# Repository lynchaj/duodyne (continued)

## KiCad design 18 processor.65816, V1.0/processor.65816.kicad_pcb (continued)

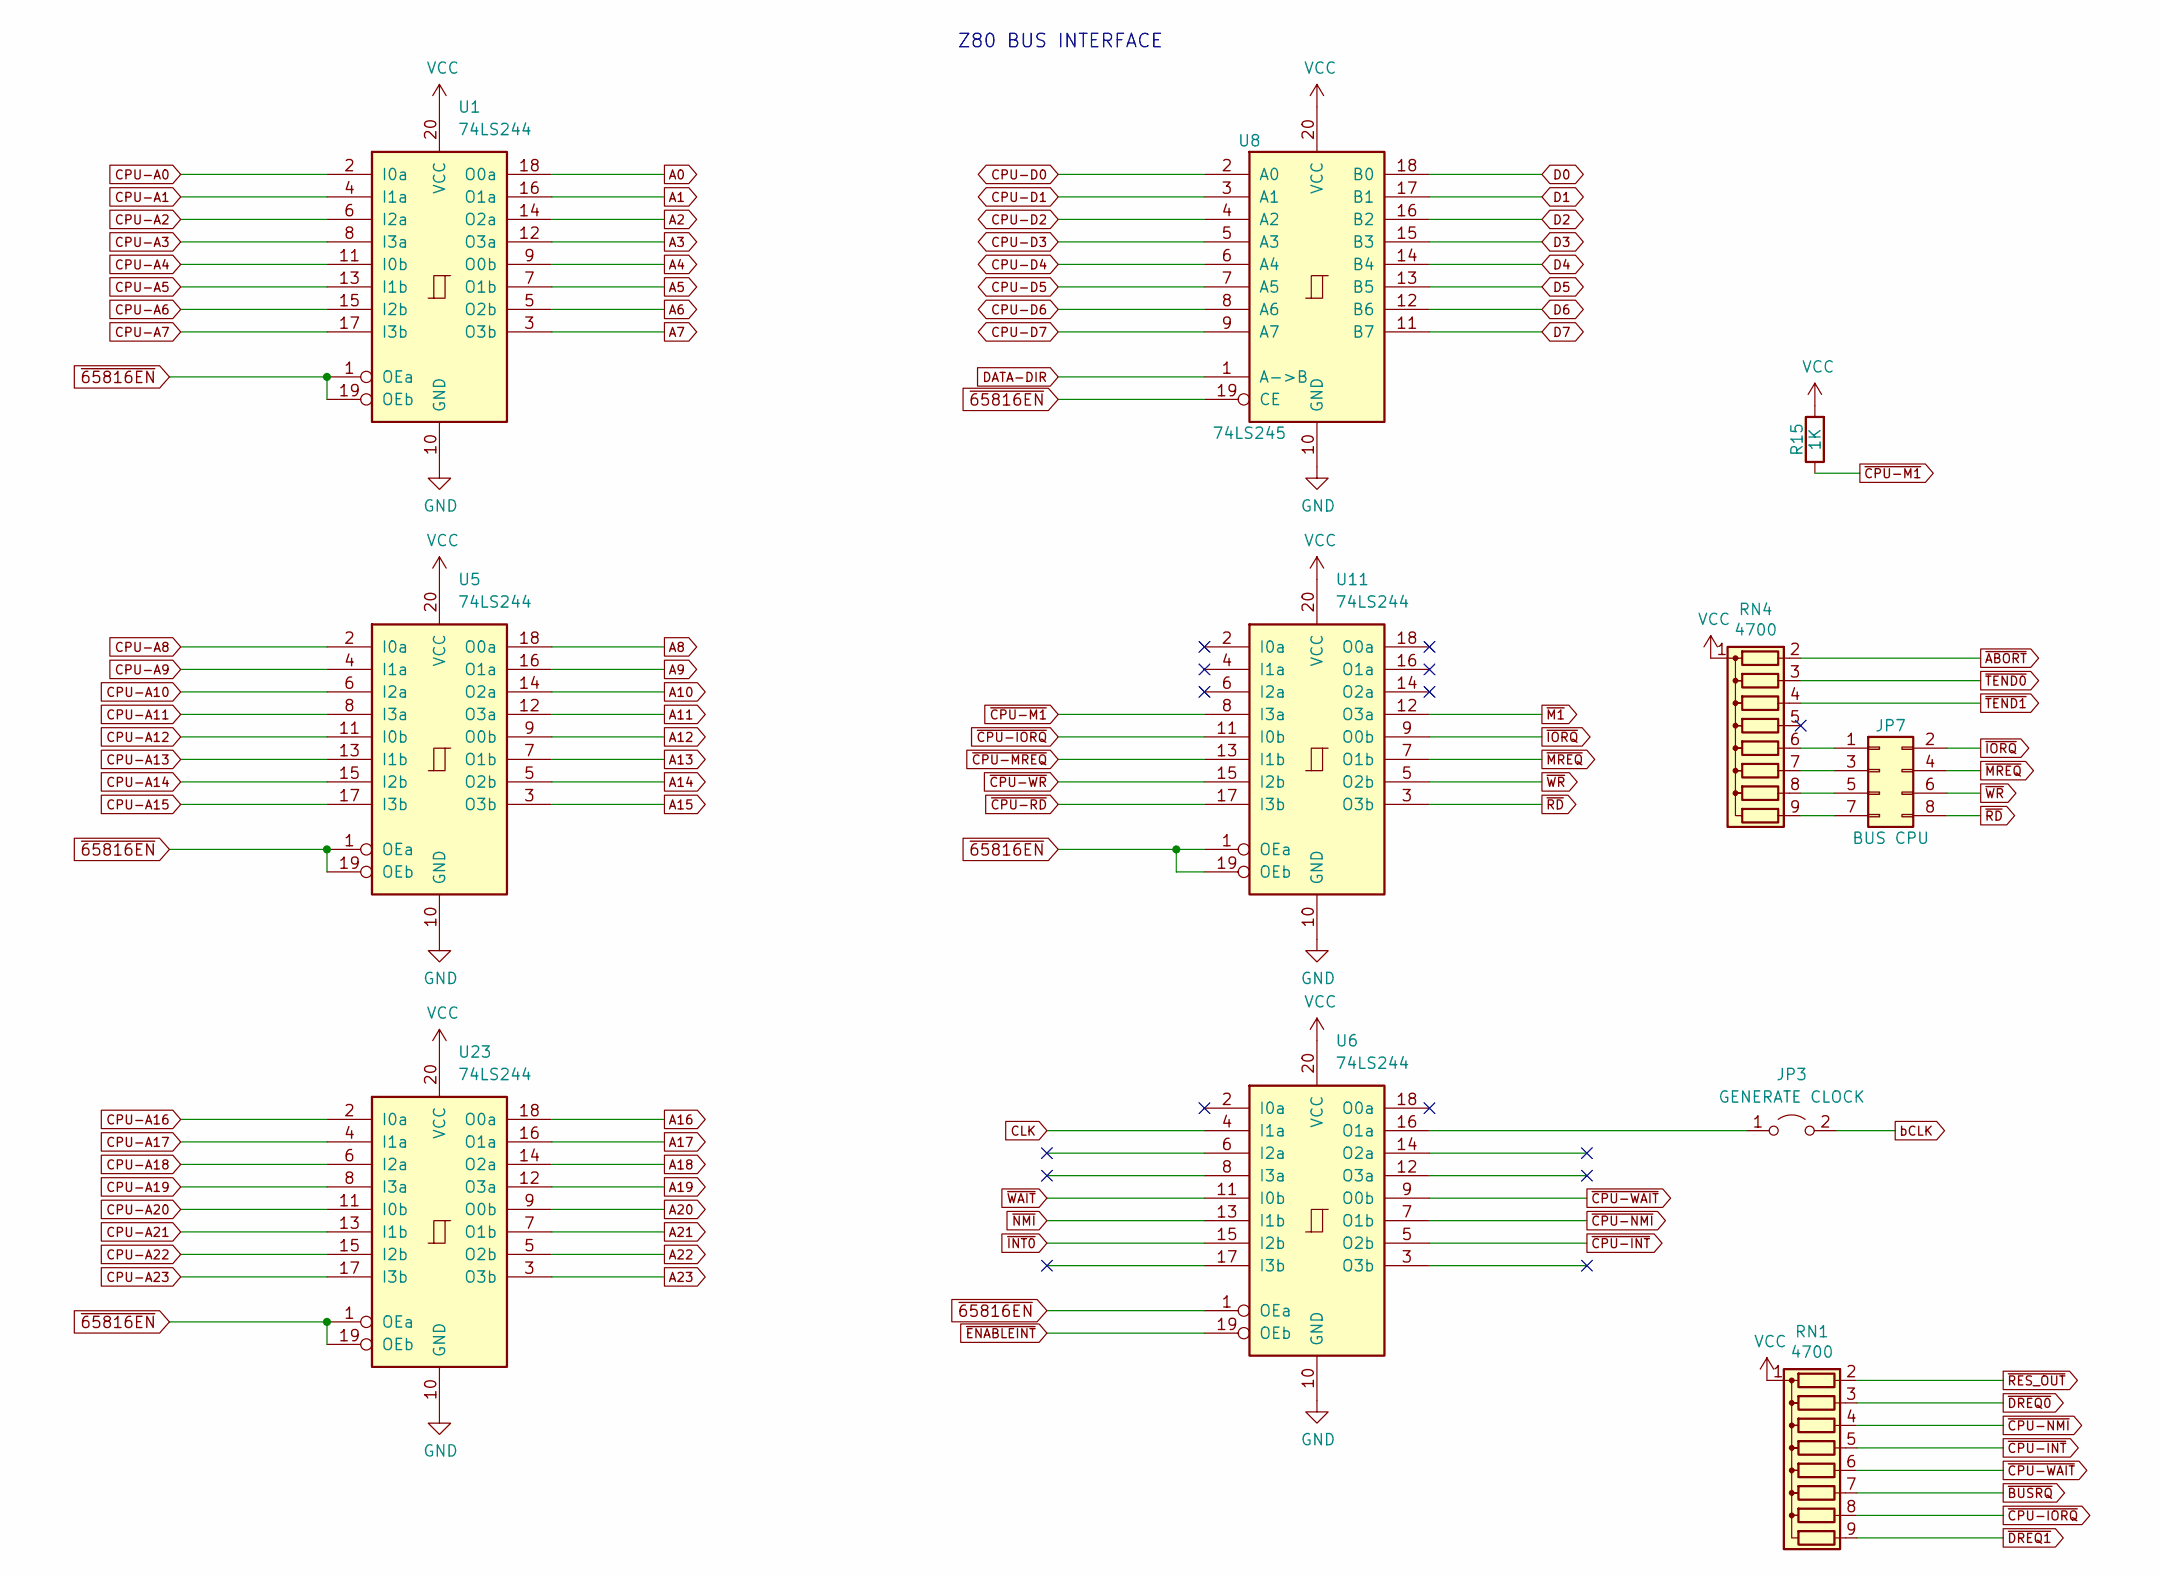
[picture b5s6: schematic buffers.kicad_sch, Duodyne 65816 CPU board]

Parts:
JP3: GENERATE CLOCK; PinHeader_1x02_P2.54mm_Vertical
JP7: BUS CPU; PinHeader_2x04_P2.54mm_Vertical
R15: 1K; R_Axial_DIN0207_L6.3mm_D2.5mm_P7.62mm_Horizontal
RN1, RN4: 4700; R_Array_SIP9
U1, U5, U6, U11, U23: 74LS244; DIP-20_W7.62mm_Socket_LongPads
U8: 74LS245; DIP-20_W7.62mm_Socket_LongPads

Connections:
A0: U1.18 (O0a); also elsewhere on the board
A1: U1.16 (O1a); also elsewhere on the board
A2: U1.14 (O2a); also elsewhere on the board
A3: U1.12 (O3a); also elsewhere on the board
A4: U1.9 (O0b); also elsewhere on the board
A5: U1.7 (O1b); also elsewhere on the board
A6: U1.5 (O2b); also elsewhere on the board
A7: U1.3 (O3b); also elsewhere on the board
A8: U5.18 (O0a); also elsewhere on the board
A9: U5.16 (O1a); also elsewhere on the board
A10: U5.14 (O2a); also elsewhere on the board
A11: U5.12 (O3a); also elsewhere on the board
A12: U5.9 (O0b); also elsewhere on the board
A13: U5.7 (O1b); also elsewhere on the board
A14: U5.5 (O2b); also elsewhere on the board
A15: U5.3 (O3b); also elsewhere on the board
A16: U23.18 (O0a); also elsewhere on the board
A17: U23.16 (O1a); also elsewhere on the board
A18: U23.14 (O2a); also elsewhere on the board
A19: U23.12 (O3a); also elsewhere on the board
A20: U23.9 (O0b); also elsewhere on the board
A21: U23.7 (O1b); also elsewhere on the board
A22: U23.5 (O2b); also elsewhere on the board
A23: U23.3 (O3b); also elsewhere on the board
CLK: U6.4 (I1a); also elsewhere on the board
CPU-A0: U1.2 (I0a); also elsewhere on the board
CPU-A1: U1.4 (I1a); also elsewhere on the board
CPU-A2: U1.6 (I2a); also elsewhere on the board
CPU-A3: U1.8 (I3a); also elsewhere on the board
CPU-A4: U1.11 (I0b); also elsewhere on the board
CPU-A5: U1.13 (I1b); also elsewhere on the board
CPU-A6: U1.15 (I2b); also elsewhere on the board
CPU-A7: U1.17 (I3b); also elsewhere on the board
CPU-A8: U5.2 (I0a); also elsewhere on the board
CPU-A9: U5.4 (I1a); also elsewhere on the board
CPU-A10: U5.6 (I2a); also elsewhere on the board
CPU-A11: U5.8 (I3a); also elsewhere on the board
CPU-A12: U5.11 (I0b); also elsewhere on the board
CPU-A13: U5.13 (I1b); also elsewhere on the board
CPU-A14: U5.15 (I2b); also elsewhere on the board
CPU-A15: U5.17 (I3b); also elsewhere on the board
CPU-A16: U23.2 (I0a); also elsewhere on the board
CPU-A17: U23.4 (I1a); also elsewhere on the board
CPU-A18: U23.6 (I2a); also elsewhere on the board
CPU-A19: U23.8 (I3a); also elsewhere on the board
CPU-A20: U23.11 (I0b); also elsewhere on the board
CPU-A21: U23.13 (I1b); also elsewhere on the board
CPU-A22: U23.15 (I2b); also elsewhere on the board
CPU-A23: U23.17 (I3b); also elsewhere on the board
CPU-D0: U8.2 (A0); also elsewhere on the board
CPU-D1: U8.3 (A1); also elsewhere on the board
CPU-D2: U8.4 (A2); also elsewhere on the board
CPU-D3: U8.5 (A3); also elsewhere on the board
CPU-D4: U8.6 (A4); also elsewhere on the board
CPU-D5: U8.7 (A5); also elsewhere on the board
CPU-D6: U8.8 (A6); also elsewhere on the board
CPU-D7: U8.9 (A7); also elsewhere on the board
D0: U8.18 (B0); also elsewhere on the board
D1: U8.17 (B1); also elsewhere on the board
D2: U8.16 (B2); also elsewhere on the board
D3: U8.15 (B3); also elsewhere on the board
D4: U8.14 (B4); also elsewhere on the board
D5: U8.13 (B5); also elsewhere on the board
D6: U8.12 (B6); also elsewhere on the board
D7: U8.11 (B7); also elsewhere on the board
DATA-DIR: U8.1 (A->B); also elsewhere on the board
GND: U1.10 (GND), U5.10 (GND), U6.10 (GND), U8.10 (GND), U11.10 (GND), U23.10 (GND); also elsewhere on the board
unnamed: JP3.1 (A), U6.16 (O1a)
unnamed: JP7.1, RN4.6 (R5)
unnamed: JP7.3, RN4.7 (R6)
unnamed: JP7.5, RN4.8 (R7)
unnamed: JP7.7, RN4.9 (R8)
VCC: R15.2, RN1.1 (common), RN4.1 (common), U1.20 (VCC), U5.20 (VCC), U6.20 (VCC), U8.20 (VCC), U11.20 (VCC), U23.20 (VCC); also elsewhere on the board
bCLK: JP3.2 (B); also elsewhere on the board
~65816EN: U1.1 (OEa), U1.19 (OEb), U5.1 (OEa), U5.19 (OEb), U6.1 (OEa), U8.19 (CE), U11.1 (OEa), U11.19 (OEb), U23.1 (OEa), U23.19 (OEb); also elsewhere on the board
~ABORT: RN4.2 (R1); also elsewhere on the board
~BUSRQ: RN1.7 (R6); also elsewhere on the board
~CPU-INT: RN1.5 (R4), U6.5 (O2b); also elsewhere on the board
~CPU-IORQ: RN1.8 (R7), U11.11 (I0b); also elsewhere on the board
~CPU-M1: R15.1, U11.8 (I3a)
~CPU-MREQ: U11.13 (I1b); also elsewhere on the board
~CPU-NMI: RN1.4 (R3), U6.7 (O1b); also elsewhere on the board
~CPU-RD: U11.17 (I3b); also elsewhere on the board
~CPU-WAIT: RN1.6 (R5), U6.9 (O0b); also elsewhere on the board
~CPU-WR: U11.15 (I2b); also elsewhere on the board
~DREQ0: RN1.3 (R2); also elsewhere on the board
~DREQ1: RN1.9 (R8); also elsewhere on the board
~ENABLEINT: U6.19 (OEb); also elsewhere on the board
~INT0: U6.15 (I2b); also elsewhere on the board
~IORQ: JP7.2, U11.9 (O0b); also elsewhere on the board
~M1: U11.12 (O3a); also elsewhere on the board
~MREQ: JP7.4, U11.7 (O1b); also elsewhere on the board
~NMI: U6.13 (I1b); also elsewhere on the board
~RD: JP7.8, U11.3 (O3b); also elsewhere on the board
~RES_OUT: RN1.2 (R1); also elsewhere on the board
~TEND0: RN4.3 (R2); also elsewhere on the board
~TEND1: RN4.4 (R3); also elsewhere on the board
~WAIT: U6.11 (I0b); also elsewhere on the board
~WR: JP7.6, U11.5 (O2b); also elsewhere on the board

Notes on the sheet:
Z80 BUS INTERFACE

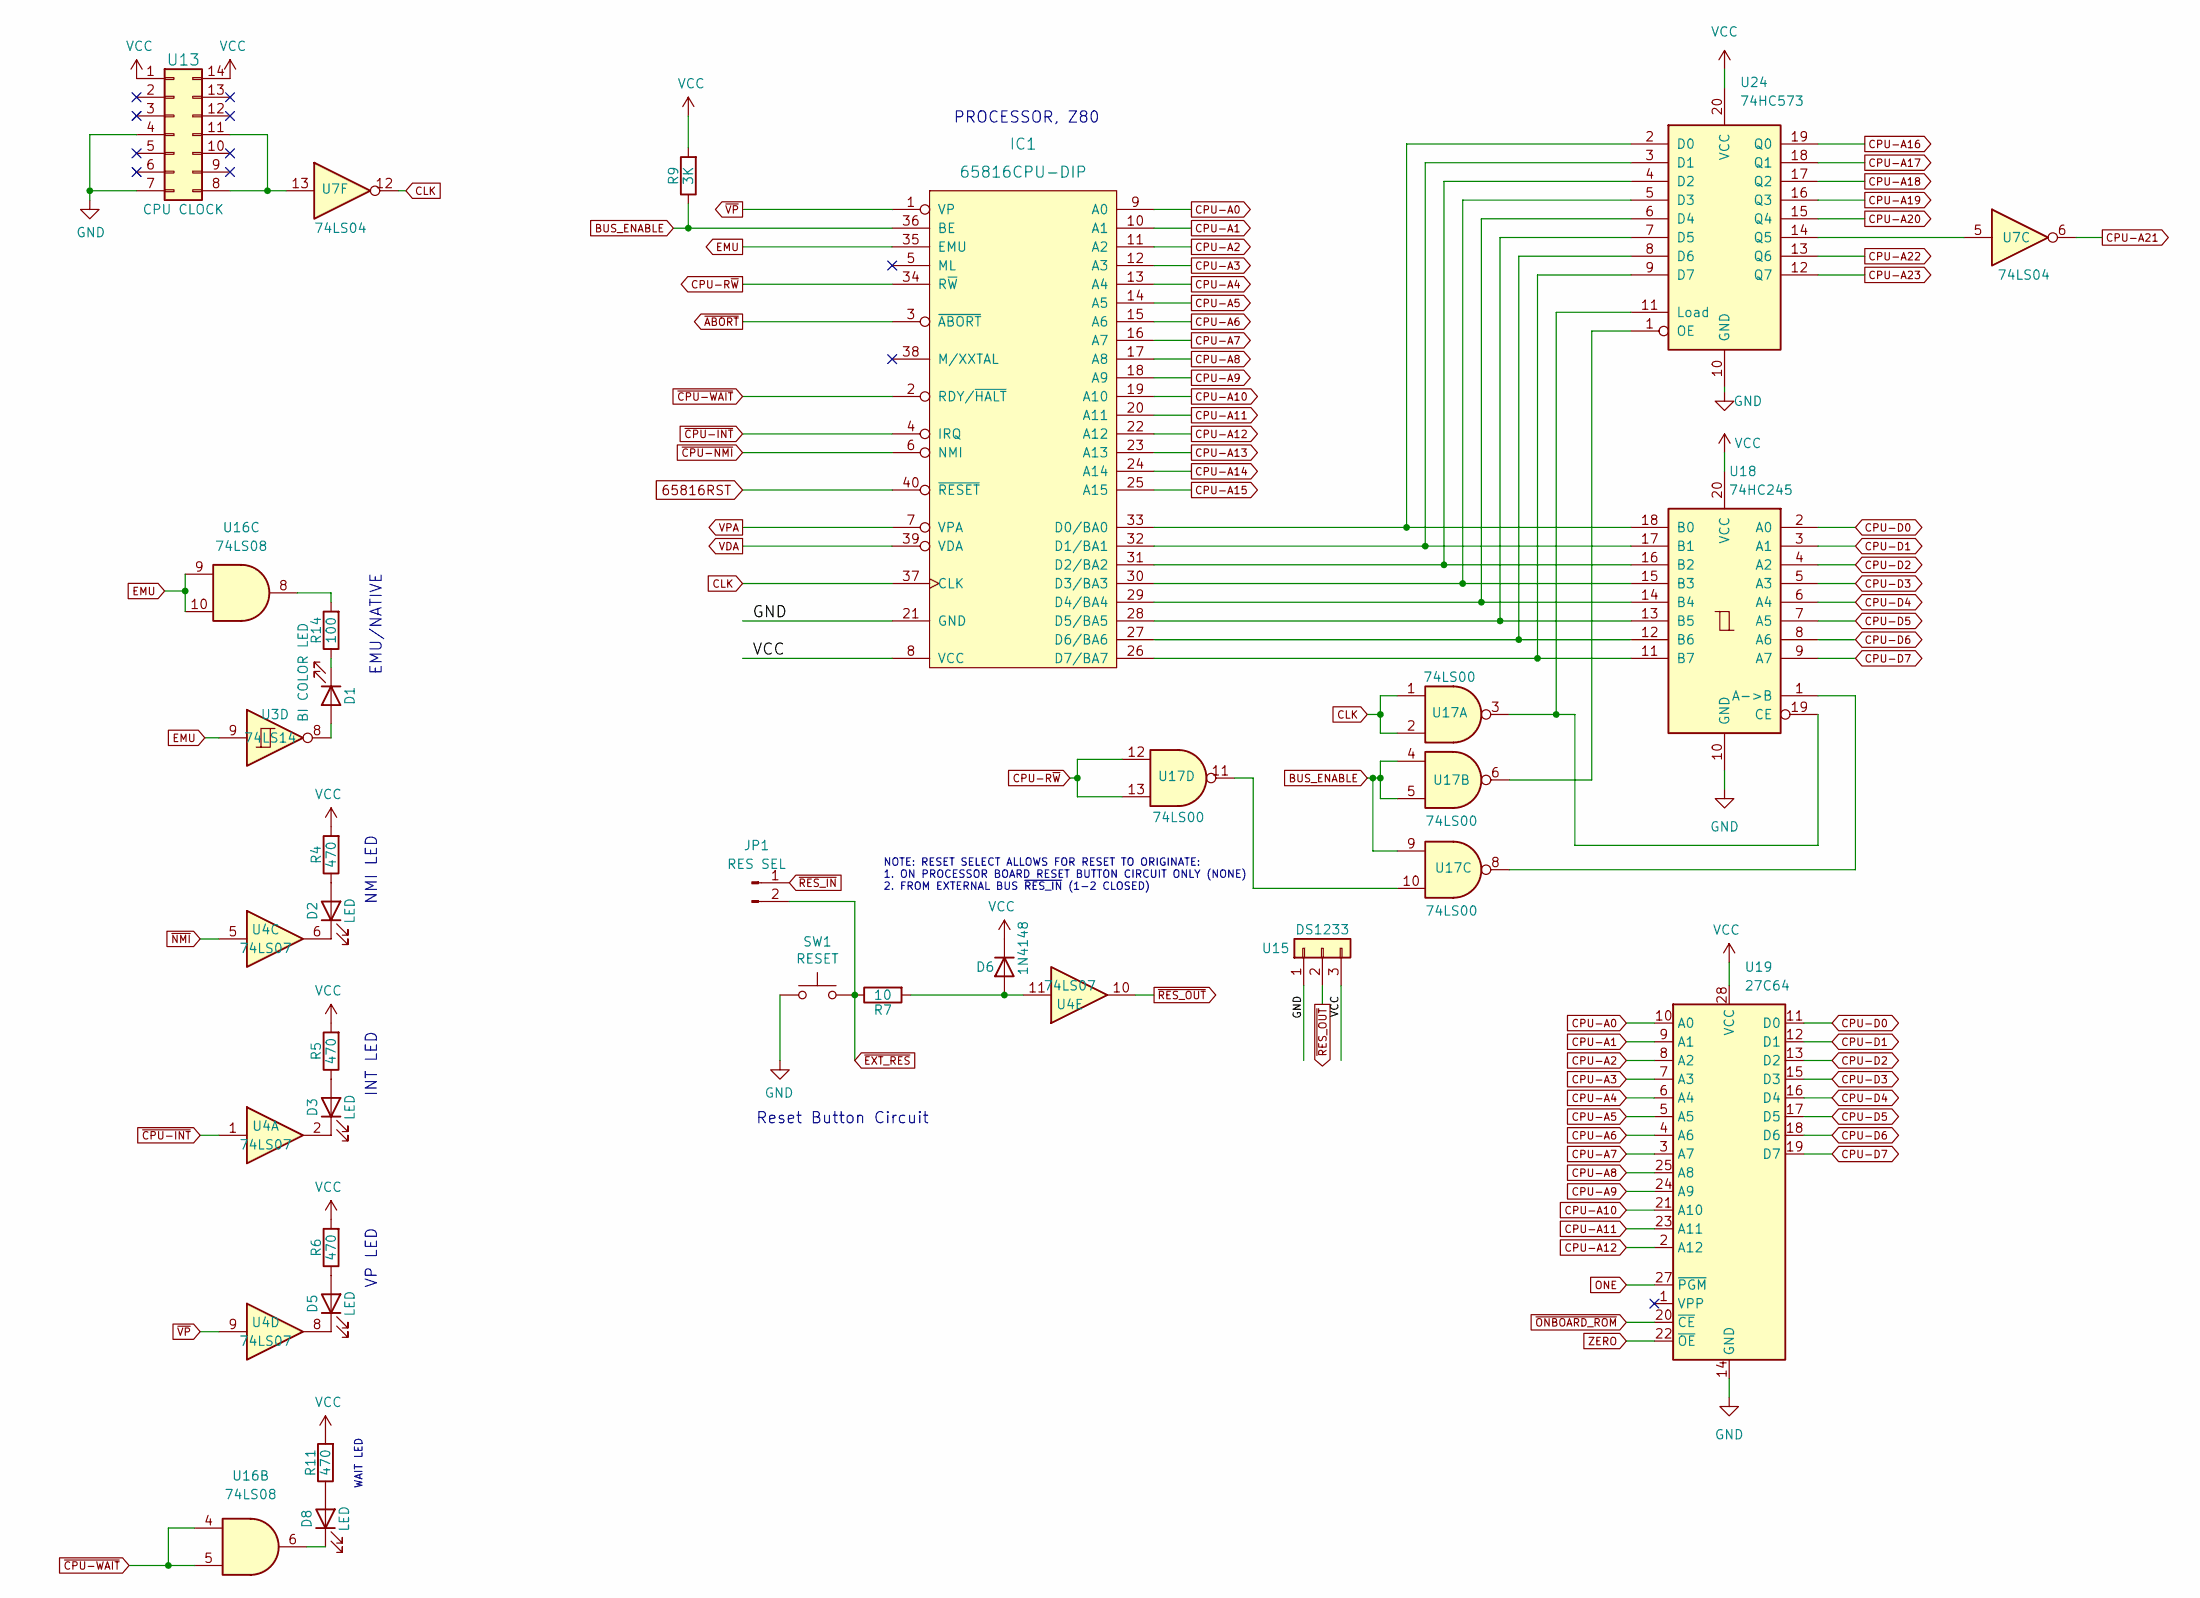
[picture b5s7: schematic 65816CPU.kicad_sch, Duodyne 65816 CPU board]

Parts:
D1: BI COLOR LED; LED_D3.0mm_Horizontal_O3.81mm_Z2.0mm
D2, D3, D5, D8: LED; LED_D3.0mm_Horizontal_O3.81mm_Z2.0mm
D6: 1N4148; D_DO-35_SOD27_P7.62mm_Horizontal
IC1: 65816CPU-DIP; DIP-40_W15.24mm_Socket_LongPads
JP1: RES SEL; PinHeader_1x02_P2.54mm_Vertical
R4, R5, R6, R11: 470; R_Axial_DIN0207_L6.3mm_D2.5mm_P7.62mm_Horizontal
R7: 10; R_Axial_DIN0207_L6.3mm_D2.5mm_P7.62mm_Horizontal
R9: 3K; R_Axial_DIN0207_L6.3mm_D2.5mm_P7.62mm_Horizontal
R14: 100; R_Axial_DIN0207_L6.3mm_D2.5mm_P7.62mm_Horizontal
SW1: RESET; SW_Tactile_SPST_Angled_PTS645Vx58-2LFS
U3: 74LS14; DIP-14_W7.62mm_Socket_LongPads
U4: 74LS07; DIP-14_W7.62mm_Socket_LongPads
U7: 74LS04; DIP-14_W7.62mm_Socket_LongPads
U13: CPU CLOCK; DIP-14_W7.62mm_Socket_LongPads
U15: DS1233; TO-92L_HandSolder
U16: 74LS08; DIP-14_W7.62mm_Socket_LongPads
U17: 74LS00; DIP-14_W7.62mm_Socket_LongPads
U18: 74HC245; DIP-20_W7.62mm_Socket_LongPads
U19: 27C64; DIP-28_W15.24mm_Socket_LongPads
U24: 74HC573; DIP-20_W7.62mm_Socket_LongPads

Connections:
65816RST: IC1.40 (~RESET); also elsewhere on the board
BUS_ENABLE: IC1.36 (BE), R9.1, U17.4, U17.5, U17.9
CLK: IC1.37 (CLK), U7.12, U17.1, U17.2; also elsewhere on the board
CPU-A0: IC1.9 (A0), U19.10 (A0); also elsewhere on the board
CPU-A1: IC1.10 (A1), U19.9 (A1); also elsewhere on the board
CPU-A2: IC1.11 (A2), U19.8 (A2); also elsewhere on the board
CPU-A3: IC1.12 (A3), U19.7 (A3); also elsewhere on the board
CPU-A4: IC1.13 (A4), U19.6 (A4); also elsewhere on the board
CPU-A5: IC1.14 (A5), U19.5 (A5); also elsewhere on the board
CPU-A6: IC1.15 (A6), U19.4 (A6); also elsewhere on the board
CPU-A7: IC1.16 (A7), U19.3 (A7); also elsewhere on the board
CPU-A8: IC1.17 (A8), U19.25 (A8); also elsewhere on the board
CPU-A9: IC1.18 (A9), U19.24 (A9); also elsewhere on the board
CPU-A10: IC1.19 (A10), U19.21 (A10); also elsewhere on the board
CPU-A11: IC1.20 (A11), U19.23 (A11); also elsewhere on the board
CPU-A12: IC1.22 (A12), U19.2 (A12); also elsewhere on the board
CPU-A13: IC1.23 (A13); also elsewhere on the board
CPU-A14: IC1.24 (A14); also elsewhere on the board
CPU-A15: IC1.25 (A15); also elsewhere on the board
CPU-A16: U24.19 (Q0); also elsewhere on the board
CPU-A17: U24.18 (Q1); also elsewhere on the board
CPU-A18: U24.17 (Q2); also elsewhere on the board
CPU-A19: U24.16 (Q3); also elsewhere on the board
CPU-A20: U24.15 (Q4); also elsewhere on the board
CPU-A21: U7.6; also elsewhere on the board
CPU-A22: U24.13 (Q6); also elsewhere on the board
CPU-A23: U24.12 (Q7); also elsewhere on the board
CPU-D0: U18.2 (A0), U19.11 (D0); also elsewhere on the board
CPU-D1: U18.3 (A1), U19.12 (D1); also elsewhere on the board
CPU-D2: U18.4 (A2), U19.13 (D2); also elsewhere on the board
CPU-D3: U18.5 (A3), U19.15 (D3); also elsewhere on the board
CPU-D4: U18.6 (A4), U19.16 (D4); also elsewhere on the board
CPU-D5: U18.7 (A5), U19.17 (D5); also elsewhere on the board
CPU-D6: U18.8 (A6), U19.18 (D6); also elsewhere on the board
CPU-D7: U18.9 (A7), U19.19 (D7); also elsewhere on the board
CPU-R~W: IC1.34 (R~W), U17.12, U17.13; also elsewhere on the board
EMU: IC1.35 (EMU), U3.9, U16.9, U16.10
GND: IC1.21 (GND), SW1.2, U13.4, U13.7, U15.1, U18.10 (GND), U19.14 (GND), U24.10 (GND); also elsewhere on the board
unnamed: D1.1 (K), R14.1
unnamed: D1.2 (A), U3.8
unnamed: D2.1 (K), U4.6
unnamed: D2.2 (A), R4.1
unnamed: D3.1 (K), U4.2
unnamed: D3.2 (A), R5.1
unnamed: D5.1 (K), U4.8
unnamed: D5.2 (A), R6.1
unnamed: D6.2 (A), R7.2, U4.11
unnamed: D8.1 (K), U16.6
unnamed: D8.2 (A), R11.1
unnamed: IC1.26 (D7/BA7), U18.11 (B7), U24.9 (D7)
unnamed: IC1.27 (D6/BA6), U18.12 (B6), U24.8 (D6)
unnamed: IC1.28 (D5/BA5), U18.13 (B5), U24.7 (D5)
unnamed: IC1.29 (D4/BA4), U18.14 (B4), U24.6 (D4)
unnamed: IC1.30 (D3/BA3), U18.15 (B3), U24.5 (D3)
unnamed: IC1.31 (D2/BA2), U18.16 (B2), U24.4 (D2)
unnamed: IC1.32 (D1/BA1), U18.17 (B1), U24.3 (D1)
unnamed: IC1.33 (D0/BA0), U18.18 (B0), U24.2 (D0)
unnamed: R14.2, U16.8
unnamed: U7.13, U13.8, U13.11
unnamed: U17.3, U18.19 (CE), U24.11 (Load)
unnamed: U17.6, U24.1 (OE)
unnamed: U17.8, U18.1 (A->B)
unnamed: U17.10, U17.11
unnamed: U7.5, U24.14 (Q5)
ONE: U19.27 (~PGM); also elsewhere on the board
VCC: D6.1 (K), IC1.8 (VCC), R4.2, R5.2, R6.2, R9.2, R11.2, U13.1, U13.14, U15.3, U18.20 (VCC), U19.28 (VCC), U24.20 (VCC); also elsewhere on the board
VDA: IC1.39 (VDA); also elsewhere on the board
VPA: IC1.7 (VPA); also elsewhere on the board
ZERO: U19.22 (~OE); also elsewhere on the board
~ABORT: IC1.3 (~ABORT); also elsewhere on the board
~CPU-INT: IC1.4 (IRQ), U4.1; also elsewhere on the board
~CPU-NMI: IC1.6 (NMI); also elsewhere on the board
~CPU-WAIT: IC1.2 (RDY/~HALT), U16.4, U16.5; also elsewhere on the board
~EXT_RES: JP1.2, R7.1, SW1.1; also elsewhere on the board
~NMI: U4.5; also elsewhere on the board
~ONBOARD_ROM: U19.20 (~CE); also elsewhere on the board
~RES_IN: JP1.1; also elsewhere on the board
~RES_OUT: U4.10, U15.2; also elsewhere on the board
~VP: IC1.1 (VP), U4.9

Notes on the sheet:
PROCESSOR, Z80
VP LED
Reset Button Circuit
WAIT LED
NMI LED
INT LED
NOTE: RESET SELECT ALLOWS FOR RESET TO ORIGINATE: 1. ON PROCESSOR BOARD RESET BUTTON CIRCUIT ONLY (NONE) 2. FROM EXTERNAL BUS ~{RES_IN} (1-2 CLOSED)
EMU/NATIVE

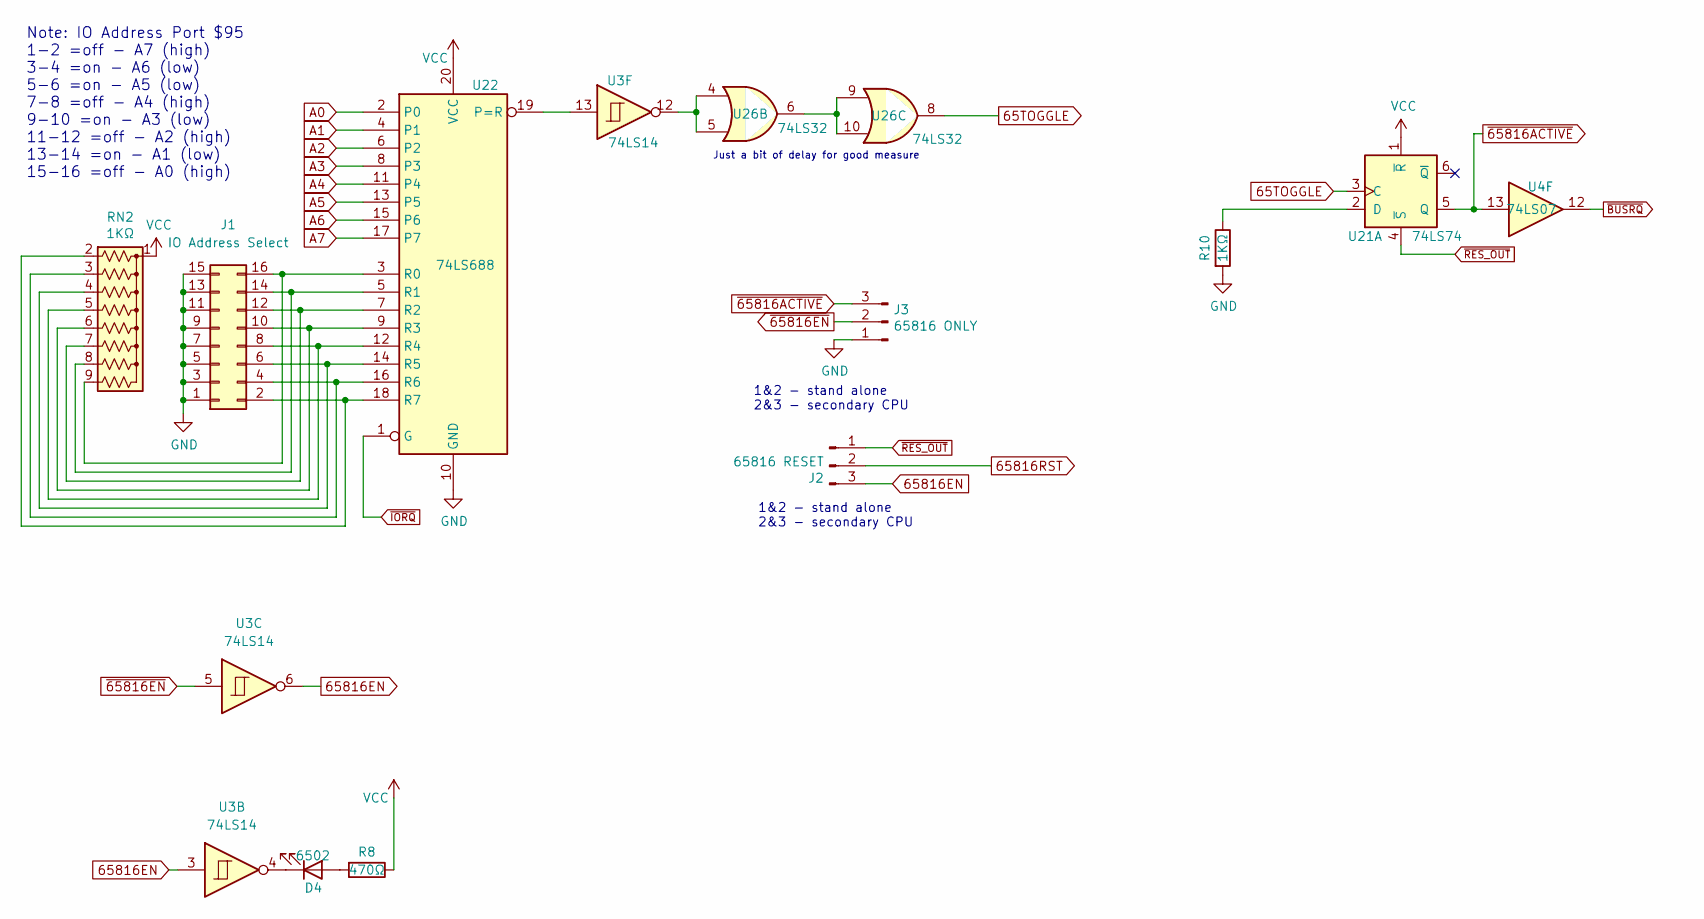
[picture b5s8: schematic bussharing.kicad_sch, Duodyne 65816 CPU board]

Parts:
D4: 6502; LED_D3.0mm_Horizontal_O3.81mm_Z2.0mm
J1: IO Address Select; PinHeader_2x08_P2.54mm_Vertical
J2: 65816 RESET; PinHeader_1x03_P2.54mm_Horizontal
J3: 65816 ONLY; PinHeader_1x03_P2.54mm_Horizontal
R8: 470Ω; R_Axial_DIN0207_L6.3mm_D2.5mm_P7.62mm_Horizontal
R10: 1KΩ; R_Axial_DIN0207_L6.3mm_D2.5mm_P7.62mm_Horizontal
RN2: 1KΩ; R_Array_SIP9
U3: 74LS14; DIP-14_W7.62mm_Socket_LongPads
U4: 74LS07; DIP-14_W7.62mm_Socket_LongPads
U21: 74LS74; DIP-14_W7.62mm_Socket_LongPads
U22: 74LS688; DIP-20_W7.62mm_Socket_LongPads
U26: 74LS32; DIP-14_W7.62mm_Socket_LongPads

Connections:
65TOGGLE: U21.3 (C), U26.8
65816EN: J2.3, U3.3, U3.6
65816RST: J2.2; also elsewhere on the board
A0: U22.2 (P0); also elsewhere on the board
A1: U22.4 (P1); also elsewhere on the board
A2: U22.6 (P2); also elsewhere on the board
A3: U22.8 (P3); also elsewhere on the board
A4: U22.11 (P4); also elsewhere on the board
A5: U22.13 (P5); also elsewhere on the board
A6: U22.15 (P6); also elsewhere on the board
A7: U22.17 (P7); also elsewhere on the board
GND: J1.1, J1.3, J1.5, J1.7, J1.9, J1.11, J1.13, J1.15, J3.1, R10.2, U22.10 (GND); also elsewhere on the board
unnamed: D4.1 (K), U3.4
unnamed: D4.2 (A), R8.2
unnamed: J1.2, RN2.2 (R1), U22.18 (R7)
unnamed: J1.4, RN2.3 (R2), U22.16 (R6)
unnamed: J1.6, RN2.4 (R3), U22.14 (R5)
unnamed: J1.8, RN2.5 (R4), U22.12 (R4)
unnamed: J1.10, RN2.6 (R5), U22.9 (R3)
unnamed: J1.12, RN2.7 (R6), U22.7 (R2)
unnamed: J1.14, RN2.8 (R7), U22.5 (R1)
unnamed: J1.16, RN2.9 (R8), U22.3 (R0)
unnamed: R10.1, U21.2 (D)
unnamed: U3.13, U22.19 (P=R)
unnamed: U3.12, U26.4, U26.5
unnamed: U26.6, U26.9, U26.10
VCC: R8.1, RN2.1 (common), U21.1 (~R), U22.20 (VCC); also elsewhere on the board
~65816ACTIVE: J3.3, U4.13, U21.5 (Q)
~65816EN: J3.2, U3.5; also elsewhere on the board
~BUSRQ: U4.12; also elsewhere on the board
~IORQ: U22.1 (G); also elsewhere on the board
~RES_OUT: J2.1, U21.4 (~S); also elsewhere on the board

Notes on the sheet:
1&2 - stand alone 2&3 - secondary CPU
Note: IO Address Port $95 1-2 =off - A7 (high) 3-4 =on - A6 (low) 5-6 =on - A5 (low) 7-8 =off - A4 (high) 9-10 =on - A3 (low) 11-12 =off - A2 (high) 13-14 =on - A1 (low) 15-16 =off - A0 (high)
Just a bit of delay for good measure

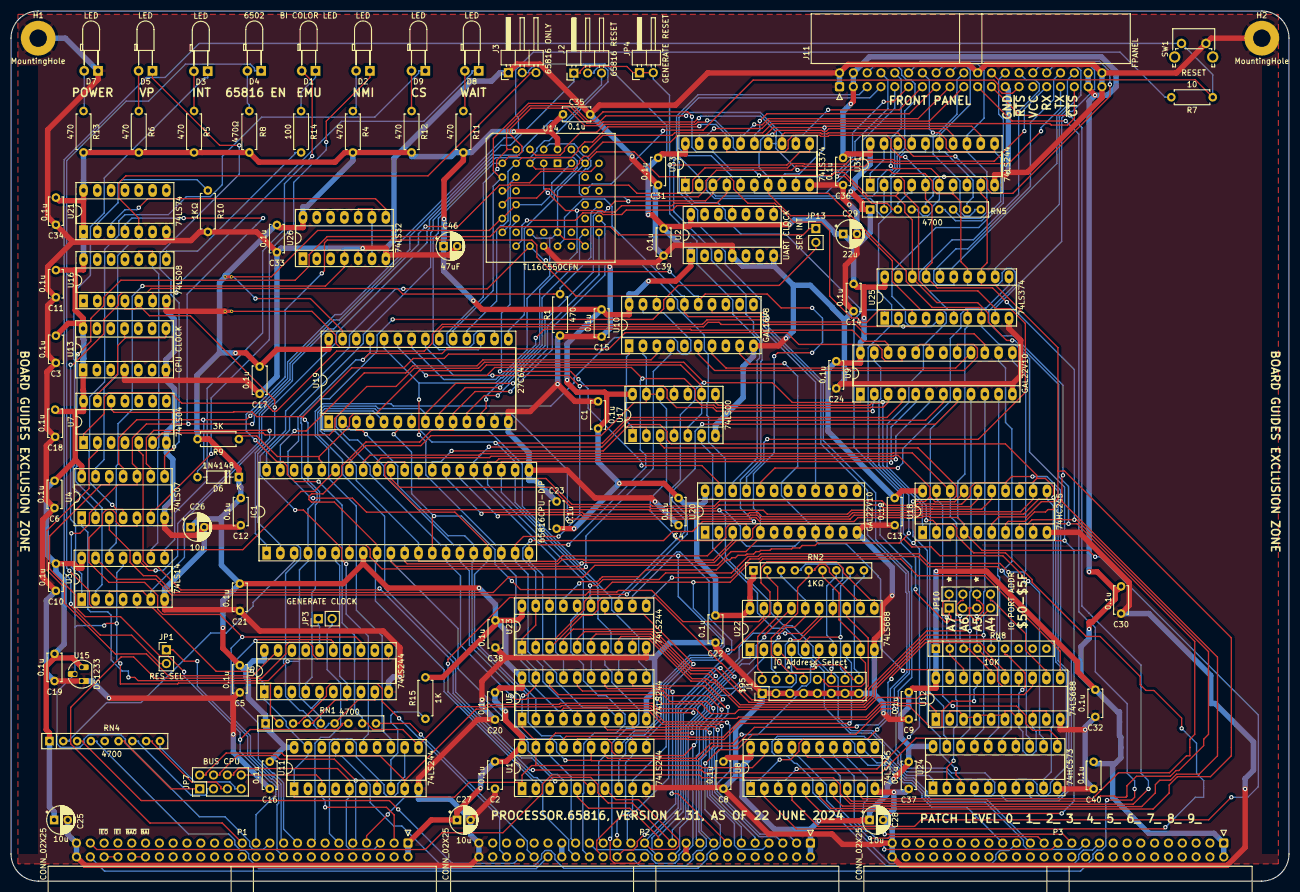
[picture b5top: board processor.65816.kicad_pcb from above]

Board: 2 copper layers, 235.0 x 160.0 mm, 114 parts (0 on the bottom side), 208 nets.

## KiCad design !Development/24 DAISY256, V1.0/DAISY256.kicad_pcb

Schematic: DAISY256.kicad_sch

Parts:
C1, C2, C3, C5, C13, C20, C21, C22, C23, C24, C25, C26, C27, C28, C29, C32, C33, C34, C35: 100nF; C_Disc_D5.0mm_W2.5mm_P5.00mm
C4, C8: 220uF; CP_Radial_D6.3mm_P2.50mm
C6, C7, C14, C15: 22pF; C_Disc_D5.0mm_W2.5mm_P5.00mm
C9, C12, C17, C18, C19: 47nF; C_Disc_D5.0mm_W2.5mm_P5.00mm
C10, C11, C30: 10uF; CP_Radial_D5.0mm_P2.00mm
C16: 22nF; C_Disc_D5.0mm_W2.5mm_P5.00mm
C31: 2.2uF; CP_Radial_Tantal_D5.0mm_P2.50mm
D1: BUSY; LED_D3.0mm
H1, H2, H3, H4: MountingHole_Pad; MountingHole_3.2mm_M3_Pad
J1: DC_JACK; BarrelJack_Horizontal
J2: DE9; DSUB-9_Female_Horizontal_P2.77x2.84mm_EdgePinOffset7.70mm_H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
J3: Audio Out; Jack_3.5mm_CUI_SJ1-3544_Horizontal
J4: TxE; PinHeader_1x02_P2.54mm_Vertical
J5: SPKR; Molex_KK-254_AE-6410-02A_1x02_P2.54mm_Vertical
J6: 32/16; PinHeader_1x03_P2.54mm_Vertical
J7: MODE; PinHeader_1x02_P2.54mm_Vertical
J8: DBM; PinHeader_1x02_P2.54mm_Vertical
J9, J12: DIL14; DIP-14_W7.62mm_Socket_LongPads
J10, J13: DIL16; DIP-16_W7.62mm_Socket_LongPads
J11, J14: DIL20; DIP-20_W7.62mm_Socket_LongPads
J15: SER ROM; PinHeader_2x04_P2.54mm_Vertical
J16: PIC ROM; PinHeader_2x08_P2.54mm_Vertical
NT1: NetTie_2; NetTie-2_THT_Pad0.3mm
P1: 10K; Potentiometer_Bourns_PTV111-1_Single_Horizontal
R1, R4, R6, R7, R14, R15, R21: 10K; R_Axial_DIN0207_L6.3mm_D2.5mm_P7.62mm_Horizontal
R2, R5, R8, R9, R10, R11, R12, R19, R20: 4.7K; R_Axial_DIN0207_L6.3mm_D2.5mm_P7.62mm_Horizontal
R13: 10R; R_Axial_DIN0207_L6.3mm_D2.5mm_P7.62mm_Horizontal
R16, R17: 1K; R_Axial_DIN0207_L6.3mm_D2.5mm_P7.62mm_Horizontal
R18: 20K; R_Axial_DIN0207_L6.3mm_D2.5mm_P7.62mm_Horizontal
SW1: RESET; SW_PUSH_6mm
U1: CTS256A-AL2; DIP-40_W15.24mm_Socket_LongPads
U2: 74LS373; DIP-20_W7.62mm_Socket_LongPads
U3, U12: 74LS138; DIP-16_W7.62mm_Socket_LongPads
U4: SP0256A-AL2; DIP-28_W15.24mm_Socket_LongPads
U5: LM324; DIP-14_W7.62mm_Socket_LongPads
U6: LM386; DIP-8_W7.62mm_Socket_LongPads
U7: MAX232; DIP-16_W7.62mm_Socket_LongPads
U8: 74LS14; DIP-14_W7.62mm_Socket_LongPads
U9: ICL7660; DIP-8_W7.62mm_Socket_LongPads
U10, U13: 2732; DIP-24_W15.24mm_Socket_LongPads
U11: 6116; DIP-24_W15.24mm_Socket_LongPads
U14: 24LC16; DIP-8_W7.62mm_Socket_LongPads
U15: PIC16F685-IP; DIP-20_W7.62mm_Socket_LongPads
U16: GAL16V8; DIP-20_W7.62mm_Socket_LongPads
Y1: 10MHz; Crystal_HC49-4H_Vertical
Y2: 3.12MHz; Crystal_HC49-U_Vertical

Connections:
-5V: C30.2, U5.11 (V-), U9.5 (VOUT)
/A0: U2.2 (O0), U4.18 (A1), U10.8 (A0), U11.8 (A0), U13.8 (A0)
/A1: U2.5 (O1), U4.17 (A2), U10.7 (A1), U11.7 (A1), U13.7 (A1)
/A2: U2.6 (O2), U4.16 (A3), U10.6 (A2), U11.6 (A2), U13.6 (A2)
/A3: U2.9 (O3), U4.15 (A4), U10.5 (A3), U11.5 (A3), U13.5 (A3)
/A4: U2.12 (O4), U4.14 (A5), U10.4 (A4), U11.4 (A4), U13.4 (A4)
/A5: U2.15 (O5), U4.13 (A6), U10.3 (A5), U11.3 (A5), U13.3 (A5)
/A6: U2.16 (O6), U4.11 (A7), U10.2 (A6), U11.2 (A6), U13.2 (A6)
/A7: U2.19 (O7), U4.10 (A8), U10.1 (A7), U11.1 (A7), U13.1 (A7)
/A8: U1.27 (A8), U10.23 (A8), U11.23 (A8), U13.23 (A8)
/A9: U1.26 (A9), U10.22 (A9), U11.22 (A9), U13.22 (A9)
/A10: U1.24 (A10), U10.19 (A10), U11.19 (A10), U13.19 (A10)
/A11: J6.1, U1.23 (A11), U13.21 (A11)
/A12: U1.22 (A12), U3.1 (A0), U12.1 (A0)
/A13: U1.21 (A13), U3.2 (A1), U12.2 (A1)
/A14: U1.20 (A14), U3.3 (A2), U12.3 (A2)
/A15: U1.19 (A15), U3.5 (E2), U12.6 (E3)
/BUSY: U7.11 (T1IN), U8.3, U8.12
/C1: J15.5, U4.4 (C1)
/C2: J15.6, U4.5 (C2)
/C3: J15.7, U4.6 (C3)
/D0: U1.28 (D0), U2.3 (D0), U10.9 (Q0), U11.9 (Q0), U13.9 (Q0)
/D1: U1.29 (D1), U2.4 (D1), U10.10 (Q1), U11.10 (Q1), U13.10 (Q1)
/D2: U1.30 (D2), U2.7 (D2), U10.11 (Q2), U11.11 (Q2), U13.11 (Q2)
/D3: U1.31 (D3), U2.8 (D3), U10.13 (Q3), U11.13 (Q3), U13.13 (Q3)
/D4: U1.32 (D4), U2.13 (D4), U10.14 (Q4), U11.14 (Q4), U13.14 (Q4)
/D5: U1.33 (D5), U2.14 (D5), U10.15 (Q5), U11.15 (Q5), U13.15 (Q5)
/D6: U1.34 (D6), U2.17 (D6), U10.16 (Q6), U11.16 (Q6), U13.16 (Q6)
/D7: U1.35 (D7), U2.18 (D7), U10.17 (Q7), U11.17 (Q7), U13.17 (Q7)
/DBM: J8.1, R21.2, U1.3 (~BUSY)
/DISABLE: J15.3, U4.3 (DISABLE)
/MODE: J7.1, R4.2, U1.36 (~MC)
/RA0: J16.2, U15.19 (C1IN+/ICSPDAT/ULPWU/AN0/RA0)
/RA1: J16.4, U15.18 (C12IN0-/ICSPCLK/Vref/AN1/RA1)
/RA2: J16.6, U15.17 (T0CKI/INT/C1OUT/AN2/RA2)
/RA3: J16.8, U15.4 (Vpp/~MCLR/RA3)
/RA4: J16.10, U15.3 (~T1G/OSC2/CLKOUT/AN3/RA4)
/RA5: J16.12, U15.2 (T1CKI/OSC1/CLKIN/RA5)
/RB5: J16.14, U15.12 (AN11/RB5)
/RB7: J16.16, U15.10 (RB7)
/RC0: J16.1, U15.16 (RC0/AN4/C2IN+)
/RC1: J16.3, U15.15 (RC1/AN5/C12IN1-)
/RC2: J16.5, U15.14 (RC2/AN6/C12IN2-/P1D)
/RC3: J16.7, U15.7 (RC3/AN7/C12IN3-/P1C)
/RC4: J16.9, U15.6 (RC4/C2OUT/P1B)
/RC5: J16.11, U15.5 (RC5/CCP1/P1A)
/RC6: J16.13, U15.8 (RC6/AN8)
/RC7: J16.15, U15.9 (RC7/AN9)
/ROM_CLK: J15.4, U4.26 (ROM_CLK)
/RW: U1.1 (~R/W), U11.21 (~WE)
/SER_IN: J15.2, U4.21 (SER_IN)
/SER_OUT: J15.1, U4.12 (SER_OUT)
/nBOOT_CS: U12.7 (O7), U13.20 (~G)
/nENABLE: U1.39 (~ENABLE), U3.4 (E1), U12.4 (E1)
/nEPROM_CS: U3.11 (O4), U10.20 (~G)
/nRAM_CS: U3.12 (O3), U11.18 (~CS)
GND: C3.2, C4.2, C6.1, C7.1, C9.2, C11.2, C12.2, C14.1, C15.1, C16.2, C20.1, C21.1, C22.1, C23.1, C24.1, C25.1, C26.1, C27.1, C28.1, C29.1, C30.1, C31.2, C32.1, C33.1, C34.1, C35.1, H1.1, H2.1, H3.1, H4.1, J1.2, J2.5, J3.S, J5.2, J7.2, J8.2, J15.8, P1.1, R15.2, SW1.1, U1.11 (OPT11), U1.40 (GND), U2.1 (OE), U2.10 (GND), U3.8 (GND), U4.1 (GND), U4.22 (TEST), U6.2 (-), U6.4 (GND), U7.15 (GND), U8.1, U8.5, U8.7 (GND), U9.3 (GND), U10.12 (GND), U10.18 (~E), U11.12 (GND), U11.20 (~OE), U12.5 (E2), U12.8 (GND), U13.12 (GND), U13.18 (~E), U14.1 (A0), U14.2 (A1), U14.3 (A2), U14.4 (GND), U15.20 (VSS), U16.10 (GND)
unnamed: C1.1, U7.5 (C2-)
unnamed: C1.2, U7.4 (C2+)
unnamed: C2.1, U7.2 (VS+)
unnamed: C3.1, U7.6 (VS-)
unnamed: C4.1, R5.2, SW1.2, U8.11
unnamed: C5.1, U7.3 (C1-)
unnamed: C5.2, U7.1 (C1+)
unnamed: C6.2, U1.17 (X2), Y1.1
unnamed: C7.2, U1.18 (X1), Y1.2
unnamed: C8.1, R13.1, U6.5
unnamed: C8.2, J3.R, J3.T
unnamed: C9.1, R13.2
unnamed: C10.1, U9.2 (CAP+)
unnamed: C10.2, U9.4 (CAP-)
unnamed: C11.1, U6.7 (BYPASS)
unnamed: C12.1, R14.2, U5.10 (+)
unnamed: C13.1, R18.2, U5.13 (-), U5.14
unnamed: C13.2, P1.3
unnamed: C14.2, U4.28 (OSC2), Y2.2
unnamed: C15.2, U4.27 (OSC1), Y2.1
unnamed: C16.1, R17.2, U5.5 (+)
unnamed: C17.1, R16.1, R17.1
unnamed: C17.2, R14.1, U5.6 (-), U5.7
unnamed: C18.1, C19.1, R18.1
unnamed: C18.2, U5.8, U5.9 (-)
unnamed: C19.2, R15.1, U5.12 (+)
unnamed: D1.1 (K), R2.2
unnamed: J2.2, U7.7 (T2OUT)
unnamed: J2.3, U7.13 (R1IN)
unnamed: J2.8, U7.14 (T1OUT)
unnamed: J3.TN, J5.1
unnamed: J4.1, U1.37 (TXD)
unnamed: J4.2, R1.2, U7.10 (T2IN)
unnamed: J6.2, U10.21 (A11)
unnamed: NT1.1, U6.6 (V+)
unnamed: P1.2, U6.3 (+)
unnamed: R2.1, U8.4
unnamed: R6.2, U14.6 (SCL), U15.11 (RB6)
unnamed: R7.2, U14.5 (SDA), U15.13 (AN10/RB4)
unnamed: R8.1, U1.6 (OPT6)
unnamed: R9.1, U1.7 (OPT7)
unnamed: R10.1, U1.8 (OPT8)
unnamed: R11.1, U1.9 (OPT9)
unnamed: R12.1, U3.6 (E3)
unnamed: R16.2, U5.1, U5.2 (-)
unnamed: R19.1, U1.10 (OPT10)
unnamed: R20.1, U1.12 (~INT3)
unnamed: U1.13 (~INT1), U4.9 (~LRQ)
unnamed: U1.14 (~RESET), U4.2 (~RESET), U4.25 (~SBY_RESET), U8.8
unnamed: U1.16 (RXD), U7.12 (R1OUT)
unnamed: U1.38 (ALATCH), U2.11 (LE)
unnamed: U3.13 (O2), U4.20 (~ALD)
unnamed: U4.8 (SBY), U8.13
unnamed: U4.24 (OUT), U5.3 (+)
unnamed: U8.9, U8.10
VCC: C2.2, C20.2, C21.2, C22.2, C23.2, C24.2, C25.2, C26.2, C27.2, C28.2, C29.2, C31.1, C32.2, C33.2, C34.2, C35.2, D1.2 (A), J1.1, J6.3, NT1.2, R1.1, R4.1, R5.1, R6.1, R7.1, R8.2, R9.2, R10.2, R11.2, R12.2, R19.2, R20.2, R21.1, U1.25 (VCC), U2.20 (VCC), U3.16 (VCC), U4.7 (VCC), U4.19 (SE), U4.23 (VD1), U5.4 (V+), U7.16 (VCC), U8.14 (VCC), U9.8 (V+), U10.24 (VCC), U11.24 (VCC), U12.16 (VCC), U13.24 (VCC), U14.7 (WP), U14.8 (VCC), U15.1 (VDD), U16.20 (VCC)

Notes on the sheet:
TXD
BOOT EPROM
SPR016 Serial Speech ROM Replacement Circuit
NOTE J7: INSTALLED FOR CTS256A-AL2 WITH DEFAULT FIRMWARE NOT INSTALLED FOR TMS7xxx OR CTS256 WITH CUSTOM FIRMWARE
CTS
DO NOT POPULATE
SPARE SOCKETS FOR DEBUGGING
RXD
NOTE: CTS256, PIC7041, PIC7001, TMS7001, TMS7041 WITH NL-4 SUFFIX ARE CLOCK QUADRUPLED (10 MHz) THOSE WITH NL-2 SUFFIX AND ALL CMOS MODELS ARE CLOCK DOUBLED (5 MHz)
NOTE: BOOT EPROM IS ONLY OPTIONAL WHEN USING CTS256 AND J7 MODE JUMPER INSTALLED. BOOT EPROM REQUIRED WHEN J7 JUMPER NOT INSTALLED AND (USING TMS7xxx OR CTS256 WITH CUSTOM FIRMWARE)
NOTE J8: ON FOR DEBUG MONITOR OFF FOR REGULAR TTS REQUIRES DEBUG MONITOR EXPANSION ROM
EXPANSION EPROM
NOTE: 6116 SRAM MUST BE INSTALLED PREFERS 200-300 NS SRAM
SPARE GAL FOR DEBUGGING
ALTERNATE MICROCONTROLLERS (SET MODE J7 TO OFF) NMOS: PIC7001 PIC7041 TMS7001 (RECOMMENDED) TMS7041 TMS7742 CMOS: TMS70C01 TMS70C02 TMS70C42 TMS70C82 TMS77C82
NOTE: J4 ON FOR SERIAL TRANSMIT OFF NO SERIAL TRANSMIT
BASED ON PUBLISHED WORK BY MECPARTS TALKER A code-to-speech board based on the General Instrument 1980s chip set https://github.com/mecparts/Talker
NOTE: DEFAULT BAUD RATE IS 9600 BAUD, 8 DATA BITS, NO PARITY, 1 STOP BITS, RTS/CTS HARDWARE HANDSHAKING (9600, 8N1)
NOTE: TALKER EXPANSION EPROM MUST BE INSTALLED
U12 AND U13 OPTIONAL WITH CTS256A-AL2 REQUIRED FOR ALTERNATE MICROCONTROLLERS
BUFFER SRAM
